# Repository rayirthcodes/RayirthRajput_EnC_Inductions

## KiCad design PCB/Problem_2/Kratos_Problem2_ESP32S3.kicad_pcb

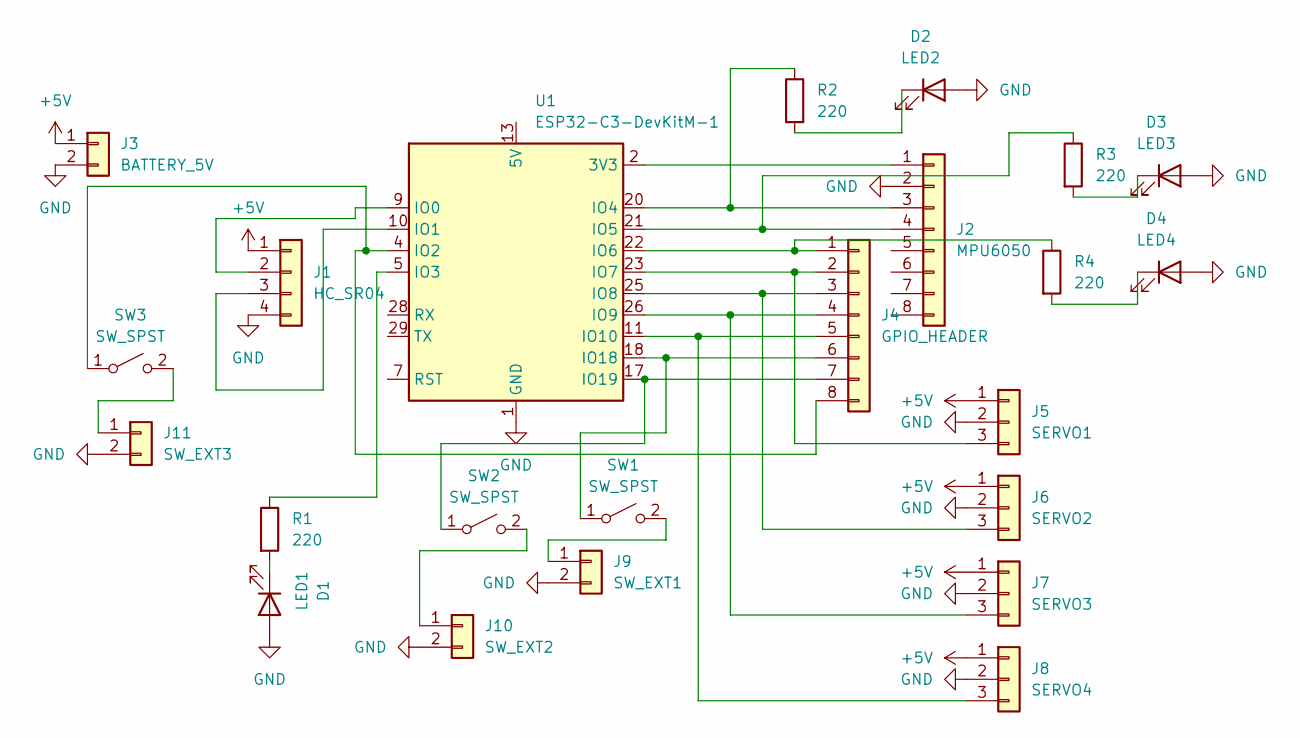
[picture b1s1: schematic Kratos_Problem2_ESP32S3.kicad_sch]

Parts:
D1: LED1; LED_D5.0mm
D2: LED2; LED_D5.0mm
D3: LED3; LED_D5.0mm
D4: LED4; LED_D5.0mm
J1: HC_SR04; HC_SR04_MODULE
J2: MPU6050; MPU6050_MODULE
J3: BATTERY_5V; PinHeader_1x02_P2.54mm_Vertical
J4: GPIO_HEADER; PinHeader_1x08_P2.54mm_Vertical
J5: SERVO1; PinHeader_1x03_P2.54mm_Vertical
J6: SERVO2; PinHeader_1x03_P2.54mm_Vertical
J7: SERVO3; PinHeader_1x03_P2.54mm_Vertical
J8: SERVO4; PinHeader_1x03_P2.54mm_Vertical
J9: SW_EXT1; PinHeader_1x02_P2.54mm_Vertical
J10: SW_EXT2; PinHeader_1x02_P2.54mm_Vertical
J11: SW_EXT3; PinHeader_1x02_P2.54mm_Vertical
R1, R2, R3, R4: 220; R_Axial_DIN0207_L6.3mm_D2.5mm_P7.62mm_Horizontal
SW1, SW2, SW3: SW_SPST; SW_Slide_SPDT_Straight_CK_OS102011MS2Q
U1: ESP32-C3-DevKitM-1

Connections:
+5V: J1.1, J3.1, J5.1, J6.1, J7.1, J8.1
GND: D1.2 (A), D2.2 (A), D3.2 (A), D4.2 (A), J1.4, J2.2, J3.2, J5.2, J6.2, J7.2, J8.2, J9.2, J10.2, J11.2, U1.1 (GND), U1.6 (GND), U1.8 (GND), U1.12 (GND), U1.15 (GND), U1.16 (GND), U1.19 (GND), U1.24 (GND), U1.27 (GND), U1.30 (GND)
unnamed: D1.1 (K), R1.2
unnamed: D2.1 (K), R2.2
unnamed: D3.1 (K), R3.2
unnamed: D4.1 (K), R4.2
unnamed: J1.2, U1.9 (IO0)
unnamed: J1.3, U1.10 (IO1)
unnamed: J2.1, U1.2 (3V3), U1.3 (3V3)
unnamed: J2.3, R2.1, U1.20 (IO4)
unnamed: J2.4, R3.1, U1.21 (IO5)
unnamed: J4.1, R4.1, U1.22 (IO6)
unnamed: J4.2, J5.3, U1.23 (IO7)
unnamed: J4.3, J6.3, U1.25 (IO8)
unnamed: J4.4, J7.3, U1.26 (IO9)
unnamed: J4.5, J8.3, U1.11 (IO10)
unnamed: J4.6, SW1.1 (A), U1.18 (IO18)
unnamed: J4.7, SW2.1 (A), U1.17 (IO19)
unnamed: J4.8, SW3.1 (A), U1.4 (IO2)
unnamed: J9.1, SW1.2 (B)
unnamed: J10.1, SW2.2 (B)
unnamed: J11.1, SW3.2 (B)
unnamed: U1.13 (5V), U1.14 (5V)
unnamed: R1.1, U1.5 (IO3)

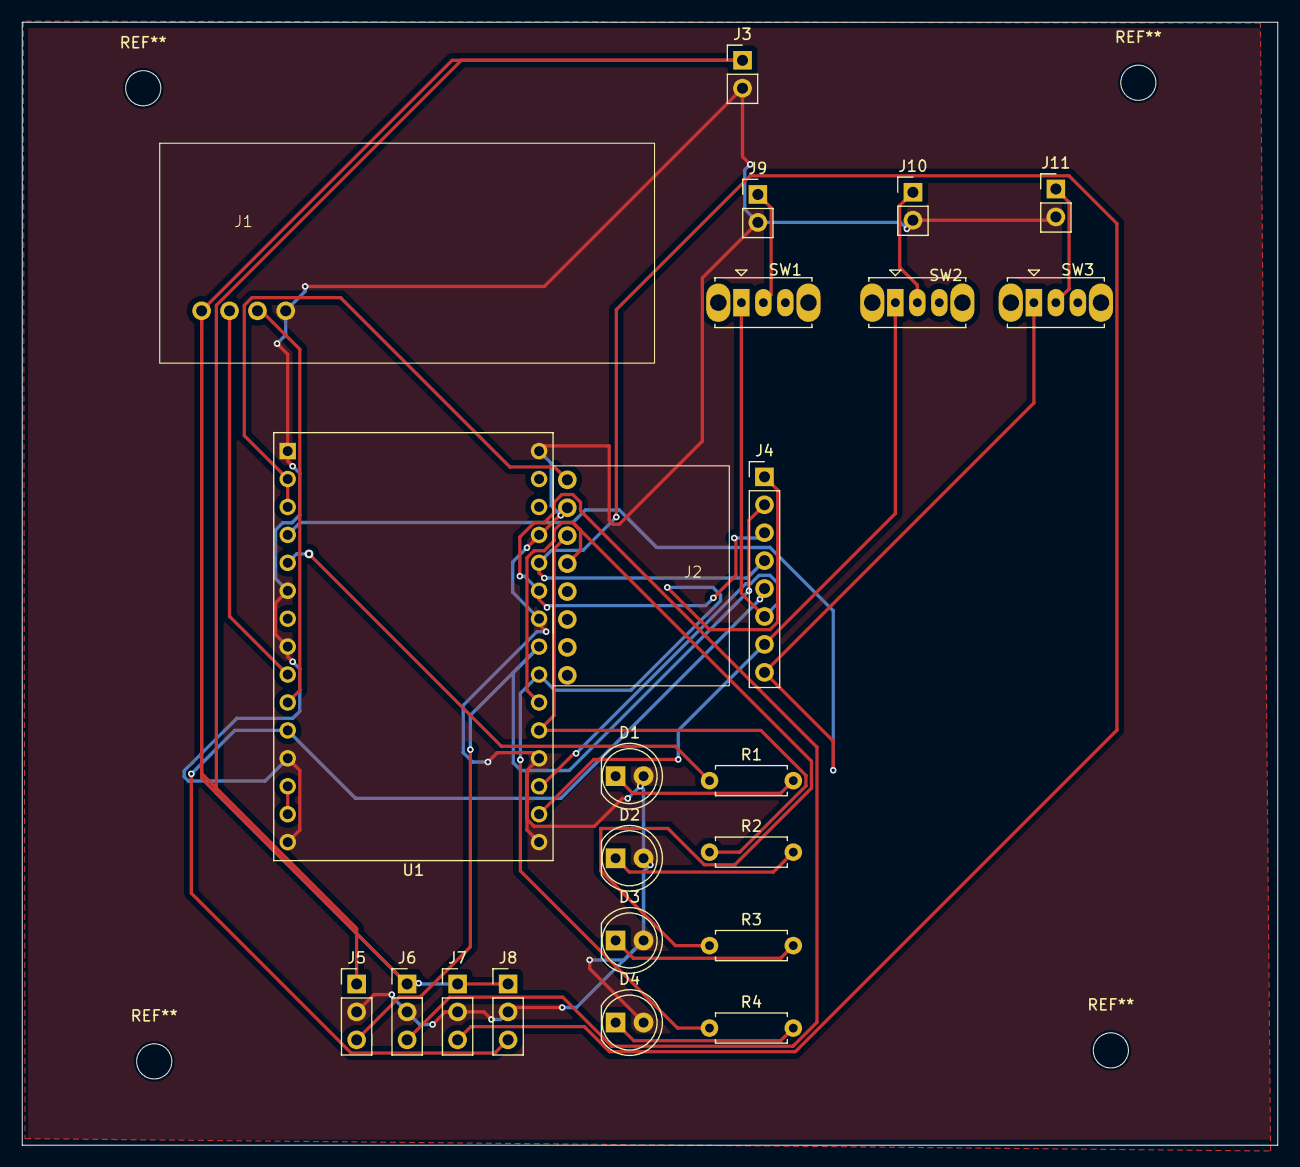
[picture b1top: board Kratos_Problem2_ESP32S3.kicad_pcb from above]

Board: 2 copper layers, 114.2 x 102.1 mm, 23 parts (0 on the bottom side), 24 nets.

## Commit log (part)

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2026-06-29 Week 2 Submission - TCA9548A Symbol and Footprint
2026-06-29 Add Week 2 custom symbol and footprint libraries
